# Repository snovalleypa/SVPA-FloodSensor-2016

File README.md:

# Photon-FloodSensor-2016
Particle.io Photon reading a MaxBotix I2CXL-MaxSonar via the I2C bus and pushing the data to the cloud, both as Particle.io events and to data.sparkfun.com. Forked from the 2016-2017 deployment of prototype flood sensors by the Snoqualmie Valley Preservation Alliance and modified to work with the Photon.

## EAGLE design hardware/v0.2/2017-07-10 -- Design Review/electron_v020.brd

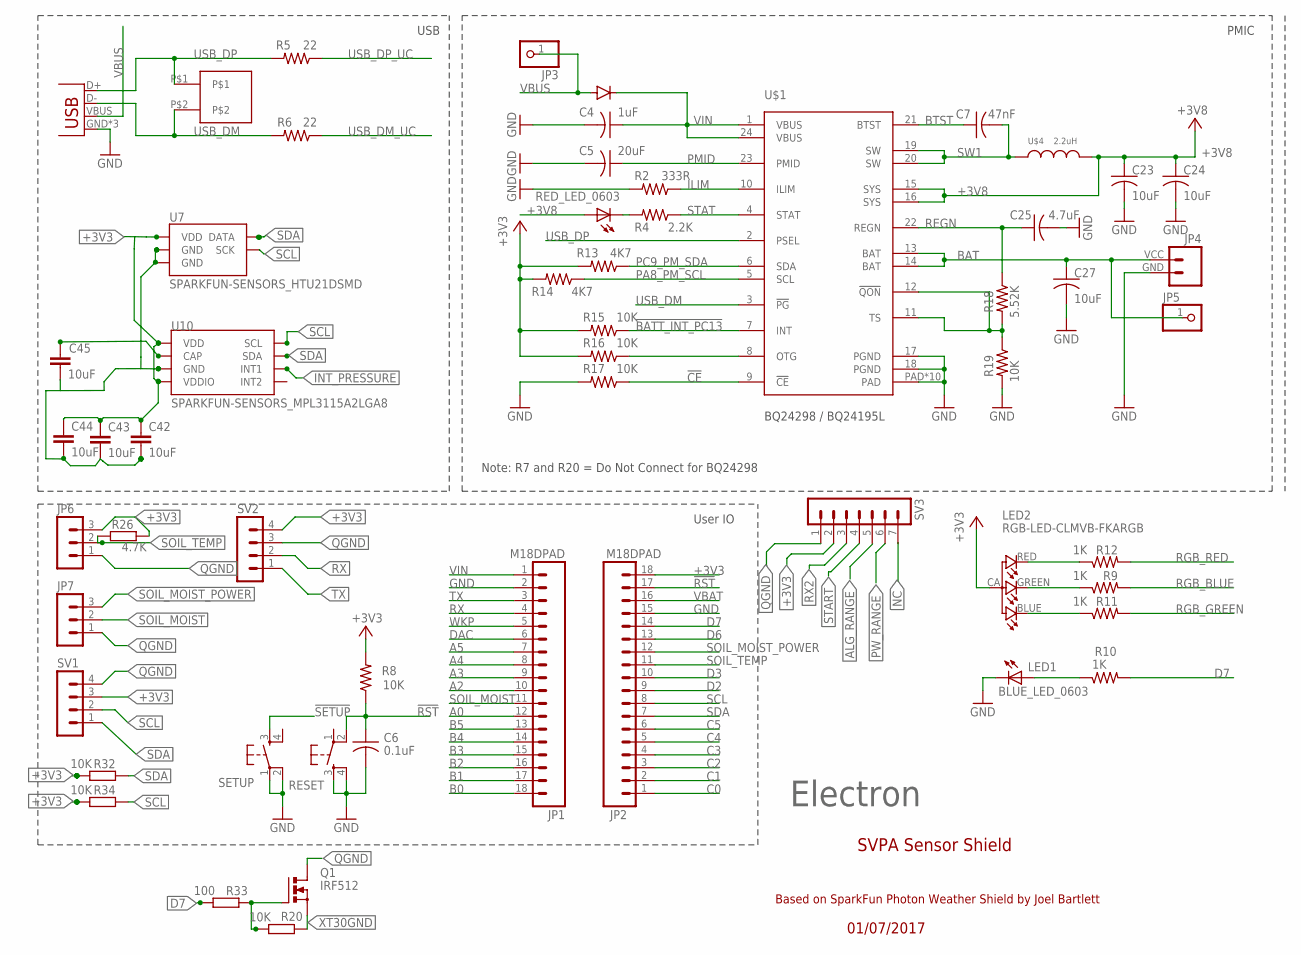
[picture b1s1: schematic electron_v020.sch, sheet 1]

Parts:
BLUE_LED_0603: LEDNOSILK; LED-0603-NS
C4: 1uF; C0603_B
C5: 20uF; C0603_B
C6: 0.1uF; C0402_B
C7: 47nF; C0402_B
C23, C24, C27: 10uF; C0603_B
C25: 4.7uF; C0603_B
C42, C43, C44, C45: 10uF; C0805
JP1, JP2: M18DPAD; 1X18-D-PADS
JP3, JP5: PINHD-1X1NOSILK; 1X01_NO_SILK
JP4: M024UCON-15767; JST-2-SMD-VERT
JP6, JP7: MA03-1
LED2: RGB-LED-CLMVB-FKARGB; PLCC4-2MM-RGB
Q1: IRF512; TO220BV
R2: 333R; R0402_B
R4: 2.2K; R0402_B
R5, R6: 22; R0402_B
R8, R15, R16, R17, R19: 10K; R0402_B
R9, R10, R11, R12: 1K; R0402_B
R13, R14: 4K7; R0402_B
R18: 5.52K; R0402_B
R20, R32, R34: 10K; R0805
R26: 4.7K; R0805
R33: 100; R0805
RED_LED_0603: LED0603; LED-0603
RESET: KMR211GLFS; TACTILE_SWITCH_SMD
SETUP: KMR211GLFS; TACTILE_SWITCH_SMD
SV1, SV2: MA04-1
SV3: MA07-1
U7: SPARKFUN-SENSORS_HTU21DSMD; SPARKFUN-SENSORS_HTU21D
U10: SPARKFUN-SENSORS_MPL3115A2LGA8; SPARKFUN-SENSORS_LGA8
U$1: BQ24298 / BQ24195L; QFN24
U$3: DIODE_NT; DIODE-DO-220AA_NT(SMP)
U$4: 2.2uH; 4020TYPE_NT
U$7: M02_0.05_HEADER
X1: USB-MICROB; USB-MICROB-SLOT-HOLE

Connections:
!BATT_INT_PC13: R15.1, U$1.7 (INT); also elsewhere on the board
!CE: R17.1, U$1.9 (!CE)
!RST: C6.1, JP2.17, R8.1, RESET.2; also elsewhere on the board
!SETUP: SETUP.3; also elsewhere on the board
+3V3: C42.1, C43.1, C44.1, JP2.18, JP6.3, LED2.CA (1), R8.2, R13.2, R14.2, R15.2, R16.2, R32.1, R34.1, SV1.3, SV2.4, U7.VDD, U10.1 (VDD), U10.4 (VDDIO); also elsewhere on the board
+3V8: C23.1, C24.1, RED_LED_0603.A, U$1.15 (SYS), U$1.16 (SYS), U$4.P$2 (2); also elsewhere on the board
A0: JP1.12; also elsewhere on the board
A2: JP1.10; also elsewhere on the board
A3: JP1.9; also elsewhere on the board
A4: JP1.8; also elsewhere on the board
A5: JP1.7; also elsewhere on the board
B0: JP1.18; also elsewhere on the board
B1: JP1.17; also elsewhere on the board
B2: JP1.16; also elsewhere on the board
B3: JP1.15; also elsewhere on the board
B4: JP1.14; also elsewhere on the board
B5: JP1.13; also elsewhere on the board
BAT: C27.1, JP4.VCC (2), JP5.1, U$1.13 (BAT), U$1.14 (BAT); also elsewhere on the board
BTST: C7.1, U$1.21 (BTST)
C0: JP2.1; also elsewhere on the board
C1: JP2.2; also elsewhere on the board
C2: JP2.3; also elsewhere on the board
C3: JP2.4; also elsewhere on the board
C4: JP2.5; also elsewhere on the board
C5: JP2.6; also elsewhere on the board
D2: JP2.9; also elsewhere on the board
D3: JP2.10; also elsewhere on the board
D6: JP2.13; also elsewhere on the board
D7: JP2.14, R10.2, R33.1; also elsewhere on the board
DAC: JP1.6; also elsewhere on the board
ILIM: R2.1, U$1.10 (ILIM)
INT_PRESSURE: U10.6 (INT1)
LED1: BLUE_LED_0603.A, R10.1
unnamed: R4.2, RED_LED_0603.C
unnamed: R16.1, U$1.8 (OTG)
unnamed: C45.1, U10.2 (CAP)
unnamed: LED2.BLUE (2), R11.1
unnamed: LED2.GREEN (3), R9.1
unnamed: Q1.G, R20.1, R33.2
unnamed: LED2.RED (4), R12.1
PA8_PM_SCL: R14.1, U$1.5 (SCL); also elsewhere on the board
PC9_PM_SDA: R13.1, U$1.6 (SDA); also elsewhere on the board
PMID: C5.1, U$1.23 (PMID)
QGND: C42.2, C43.2, C44.2, JP6.1, JP7.1, Q1.D, SV1.4, SV2.3, U7.7 (GND), U7.GND, U10.3 (GND)
REGN: C25.1, R18.1, U$1.22 (REGN)
RGB_BLUE: R11.2; also elsewhere on the board
RGB_GREEN: R9.2; also elsewhere on the board
RGB_RED: R12.2; also elsewhere on the board
RX: JP1.4, SV2.2; also elsewhere on the board
SCL: JP2.8, R34.2, SV1.2, U7.SCK, U10.8 (SCL)
SDA: JP2.7, R32.2, SV1.1, U10.7 (SDA)
SOIL_MOIST: JP1.11, JP7.2
SOIL_MOIST_POWER: JP2.12, JP7.3
SOIL_TEMP: JP2.11, JP6.2
STAT: R4.1, U$1.4 (STAT)
SW1: C7.2, U$1.19 (SW), U$1.20 (SW), U$4.P$1 (1)
TS: R18.2, R19.1, U$1.11 (TS), U$1.12 (!QON)
TX: JP1.3, SV2.1; also elsewhere on the board
USB_DM: R6.2, U$1.3 (!PG), U$7.P$2, X1.D-
USB_DM_UC: R6.1; also elsewhere on the board
USB_DP: R5.2, U$1.2 (PSEL), U$7.P$1, X1.D+
USB_DP_UC: R5.1; also elsewhere on the board
VBAT: JP2.16; also elsewhere on the board
VBUS: JP3.1, U$3.ANODE, X1.VBUS
VIN: C4.1, JP1.1, U$1.1 (VBUS), U$1.24 (VBUS), U$3.CATHODE
WKP: JP1.5; also elsewhere on the board

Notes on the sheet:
PMIC
User IO
USB
Electron
Note: R7 and R20 = Do Not Connect for BQ24298
01/07/2017
SVPA Sensor Shield
Based on SparkFun Photon Weather Shield by Joel Bartlett

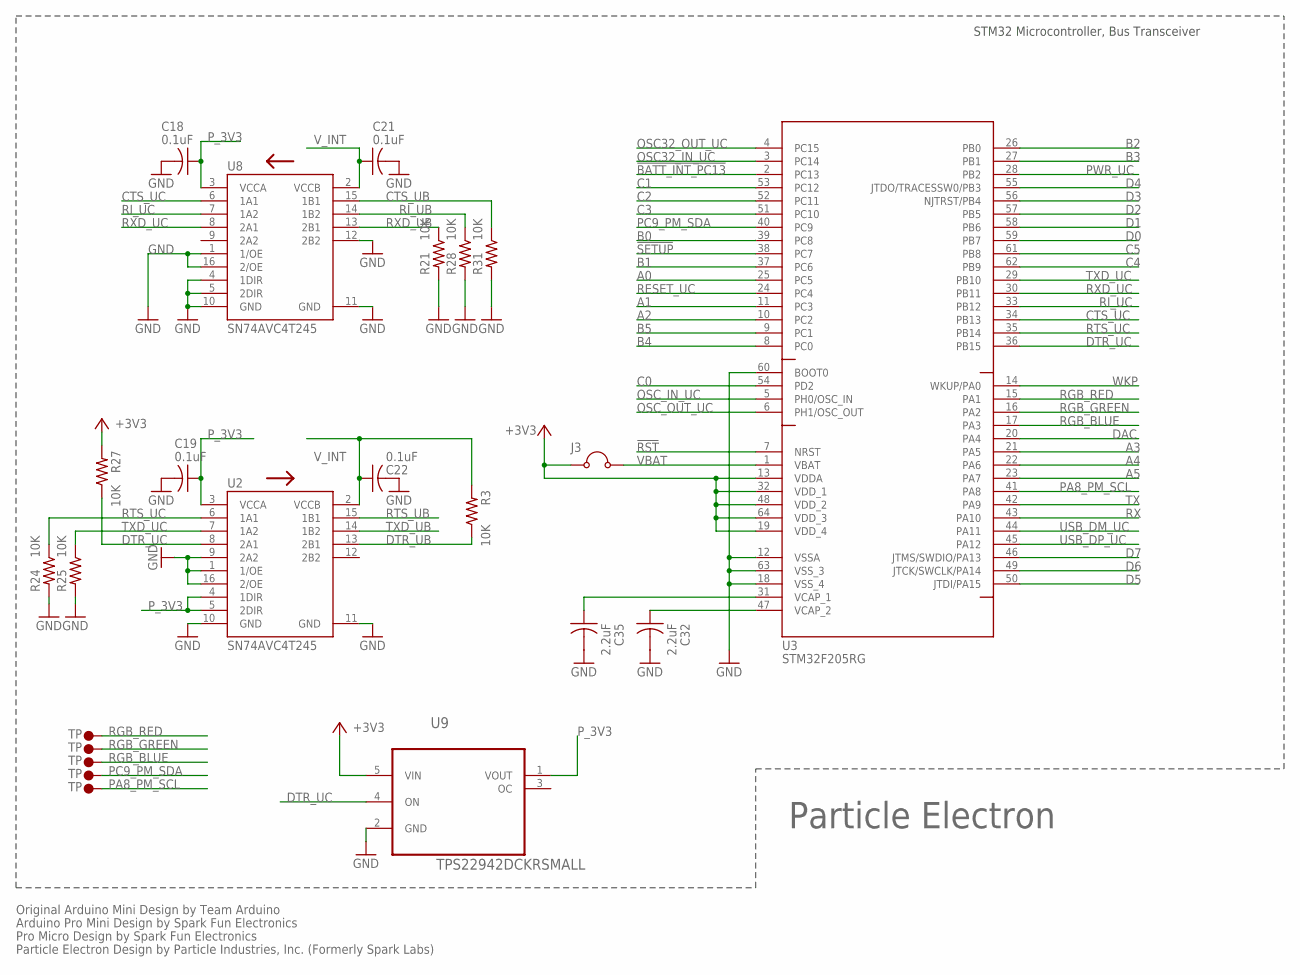
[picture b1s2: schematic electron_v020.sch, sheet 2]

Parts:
C18, C19, C21, C22: 0.1uF; C0402_B
C32, C35: 2.2uF; C0402_B
J3: JUMPER_NC_SMD; JUMPER_SMD_NC
R3, R21, R24, R25, R27, R28, R31: 10K; R0402_B
U2, U8: SN74AVC4T245; UFQFN-16
U3: STM32F205RG; LQFP64
U9: TPS22942DCKRSMALL; SC70-5
U$8, U$9, U$11, U$12, U$13: TP0; TP30_BOT

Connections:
!BATT_INT_PC13: U3.2 (PC13); also elsewhere on the board
!RST: U3.7 (NRST); also elsewhere on the board
!SETUP: U3.38 (PC7); also elsewhere on the board
+3V3: J3.1, R27.2, U3.13 (VDDA), U3.19 (VDD_4), U3.32 (VDD_1), U3.48 (VDD_2), U3.64 (VDD_3), U9.5 (VIN); also elsewhere on the board
A0: U3.25 (PC5); also elsewhere on the board
A1: U3.11 (PC3)
A2: U3.10 (PC2); also elsewhere on the board
A3: U3.21 (PA5); also elsewhere on the board
A4: U3.22 (PA6); also elsewhere on the board
A5: U3.23 (PA7); also elsewhere on the board
B0: U3.39 (PC8); also elsewhere on the board
B1: U3.37 (PC6); also elsewhere on the board
B2: U3.26 (PB0); also elsewhere on the board
B3: U3.27 (PB1); also elsewhere on the board
B4: U3.8 (PC0); also elsewhere on the board
B5: U3.9 (PC1); also elsewhere on the board
C0: U3.54 (PD2); also elsewhere on the board
C1: U3.53 (PC12); also elsewhere on the board
C2: U3.52 (PC11); also elsewhere on the board
C3: U3.51 (PC10); also elsewhere on the board
C4: U3.62 (PB9); also elsewhere on the board
C5: U3.61 (PB8); also elsewhere on the board
CTS_UB: R31.1, U8.15 (1B1); also elsewhere on the board
CTS_UC: U3.34 (PB13), U8.6 (1A1)
D0: U3.59 (PB7)
D1: U3.58 (PB6)
D2: U3.57 (PB5); also elsewhere on the board
D3: U3.56 (NJTRST/PB4); also elsewhere on the board
D4: U3.55 (JTDO/TRACESSW0/PB3)
D5: U3.50 (JTDI/PA15)
D6: U3.49 (JTCK/SWCLK/PA14); also elsewhere on the board
D7: U3.46 (JTMS/SWDIO/PA13); also elsewhere on the board
DAC: U3.20 (PA4); also elsewhere on the board
DTR_UB: R3.1, U2.13 (2B1); also elsewhere on the board
DTR_UC: R27.1, U2.8 (2A1), U3.36 (PB15), U9.4 (ON)
unnamed: C35.1, U3.31 (VCAP_1)
unnamed: C32.1, U3.47 (VCAP_2)
OSC32_IN_UC: U3.3 (PC14); also elsewhere on the board
OSC32_OUT_UC: U3.4 (PC15); also elsewhere on the board
OSC_IN_UC: U3.5 (PH0/OSC_IN); also elsewhere on the board
OSC_OUT_UC: U3.6 (PH1/OSC_OUT); also elsewhere on the board
PA8_PM_SCL: U3.41 (PA8), U$9.P$1; also elsewhere on the board
PC9_PM_SDA: U3.40 (PC9), U$8.P$1; also elsewhere on the board
PWR_UC: U3.28 (PB2); also elsewhere on the board
P_3V3: C18.1, C19.1, U2.3 (VCCA), U2.4 (1DIR), U2.5 (2DIR), U8.3 (VCCA), U9.1 (VOUT)
RESET_UC: U3.24 (PC4); also elsewhere on the board
RGB_BLUE: U3.17 (PA3), U$13.P$1; also elsewhere on the board
RGB_GREEN: U3.16 (PA2), U$12.P$1; also elsewhere on the board
RGB_RED: U3.15 (PA1), U$11.P$1; also elsewhere on the board
RI_UB: R28.1, U8.14 (1B2); also elsewhere on the board
RI_UC: U3.33 (PB12), U8.7 (1A2)
RTS_UB: U2.15 (1B1); also elsewhere on the board
RTS_UC: R24.1, U2.6 (1A1), U3.35 (PB14)
RX: U3.43 (PA10); also elsewhere on the board
RXD_UB: R21.1, U8.13 (2B1); also elsewhere on the board
RXD_UC: U3.30 (PB11), U8.8 (2A1)
TX: U3.42 (PA9); also elsewhere on the board
TXD_UB: U2.14 (1B2); also elsewhere on the board
TXD_UC: R25.1, U2.7 (1A2), U3.29 (PB10)
USB_DM_UC: U3.44 (PA11); also elsewhere on the board
USB_DP_UC: U3.45 (PA12); also elsewhere on the board
VBAT: J3.2, U3.1 (VBAT); also elsewhere on the board
V_INT: C21.1, C22.1, R3.2, U2.2 (VCCB), U8.2 (VCCB); also elsewhere on the board
WKP: U3.14 (WKUP/PA0); also elsewhere on the board

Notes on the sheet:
Particle Electron
STM32 Microcontroller, Bus Transceiver
Original Arduino Mini Design by Team Arduino
Arduino Pro Mini Design by Spark Fun Electronics
Pro Micro Design by Spark Fun Electronics
Particle Electron Design by Particle Industries, Inc. (Formerly Spark Labs)

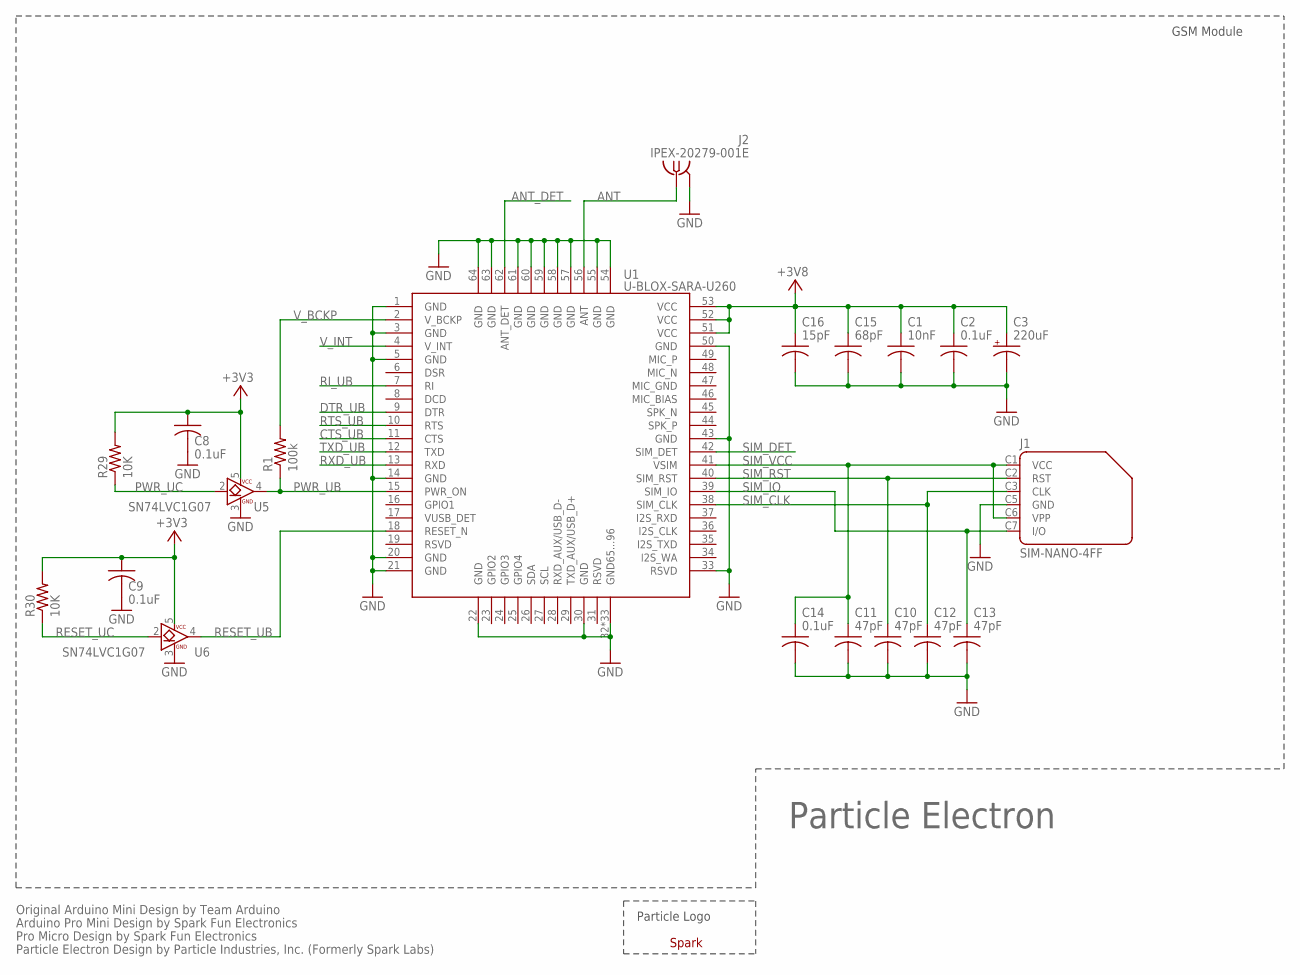
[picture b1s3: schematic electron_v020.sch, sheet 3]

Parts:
C1: 10nF; C0402_B
C2, C8, C9, C14: 0.1uF; C0402_B
C3: 220uF; C/6032-28R
C10, C11, C12, C13: 47pF; C0402_B
C15: 68pF; C0402_B
C16: 15pF; C0402_B
J1: SIM-NANO-4FF; GCT-SIM8100
J2: IPEX-20279-001E
R1: 100k; R0402_B
R29, R30: 10K; R0402_B
U1: U-BLOX-SARA-U260; U-BLOX-SARA-U2
U5, U6: SN74LVC1G07; SC-70-5
U$2: SPARK_LOGO2

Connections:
+3V3: C8.1, C9.1, R29.2, R30.2, U5.5 (VCC), U6.5 (VCC); also elsewhere on the board
+3V8: C1.1, C2.1, C3.+, C15.1, C16.1, U1.51 (VCC), U1.52 (VCC), U1.53 (VCC); also elsewhere on the board
ANT: J2.1, U1.56 (ANT)
ANT_DET: U1.62 (ANT_DET)
CTS_UB: U1.11 (CTS); also elsewhere on the board
DTR_UB: U1.9 (DTR); also elsewhere on the board
PWR_UB: R1.1, U1.15 (PWR_ON), U5.4 (B)
PWR_UC: R29.1, U5.2 (A); also elsewhere on the board
RESET_UB: U1.18 (RESET_N), U6.4 (B)
RESET_UC: R30.1, U6.2 (A); also elsewhere on the board
RI_UB: U1.7 (RI); also elsewhere on the board
RTS_UB: U1.10 (RTS); also elsewhere on the board
RXD_UB: U1.13 (RXD); also elsewhere on the board
SIM_CLK: C12.1, J1.C3 (CLK), U1.38 (SIM_CLK)
SIM_DET: U1.42 (SIM_DET)
SIM_IO: C13.1, J1.C7 (I/O), U1.39 (SIM_IO)
SIM_RST: C10.1, J1.C2 (RST), U1.40 (SIM_RST)
SIM_VCC: C11.1, C14.1, J1.C1 (VCC), J1.C6 (VPP), U1.41 (VSIM)
TXD_UB: U1.12 (TXD); also elsewhere on the board
V_BCKP: R1.2, U1.2 (V_BCKP)
V_INT: U1.4 (V_INT); also elsewhere on the board

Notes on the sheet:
Particle Electron
GSM Module
Particle Logo
Original Arduino Mini Design by Team Arduino
Arduino Pro Mini Design by Spark Fun Electronics
Pro Micro Design by Spark Fun Electronics
Particle Electron Design by Particle Industries, Inc. (Formerly Spark Labs)

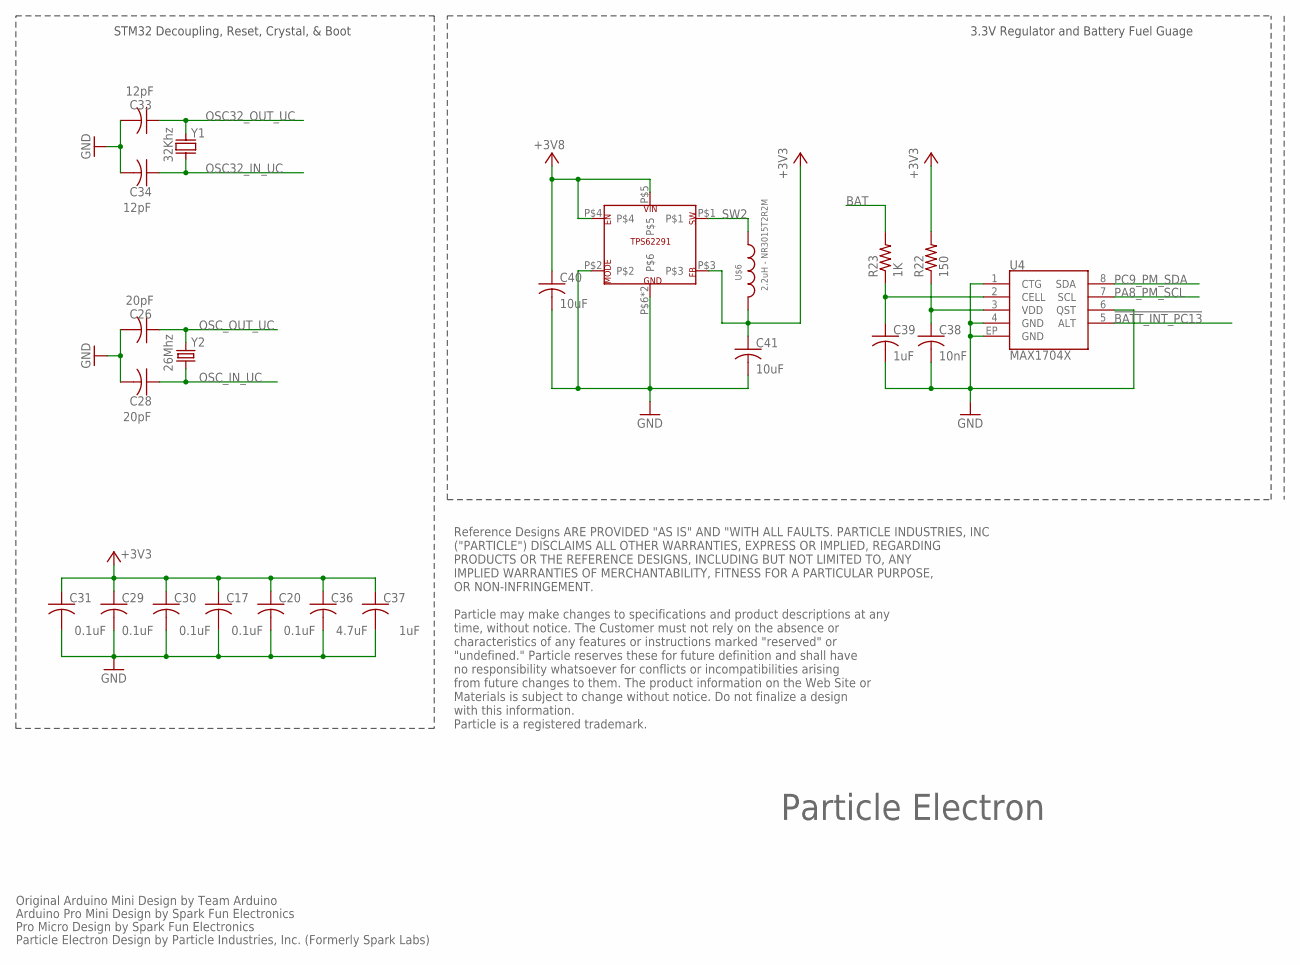
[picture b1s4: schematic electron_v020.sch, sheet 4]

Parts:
C17, C20, C29, C30, C31: 0.1uF; C0402_B
C26, C28: 20pF; C0402_B
C33, C34: 12pF; C0402_B
C36: 4.7uF; C0402_B
C37, C39: 1uF; C0402_B
C38: 10nF; C0402_B
C40, C41: 10uF; C0603_B
R22: 150; 0603-RES
R23: 1K; 0603-RES
U4: MAX1704X; TDFN-8
U$5: TPS62291DRV; S-PWSON-N6
U$6: 2.2uH - NR3015T2R2M; INDUCTOR-NR3015
Y1: 32Khz; FC135
Y2: 26Mhz; CRYSTAL-SMD-5X3

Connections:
!BATT_INT_PC13: U4.5 (ALT); also elsewhere on the board
+3V3: C17.1, C20.1, C29.1, C30.1, C31.1, C36.1, C37.1, C41.1, R22.2, U$5.P$3, U$6.2; also elsewhere on the board
+3V8: C40.1, U$5.P$4, U$5.P$5; also elsewhere on the board
BAT: R23.2; also elsewhere on the board
unnamed: C39.1, R23.1, U4.2 (CELL)
unnamed: C38.1, R22.1, U4.3 (VDD)
OSC32_IN_UC: C34.1, Y1.X1 (1); also elsewhere on the board
OSC32_OUT_UC: C33.1, Y1.X2 (2); also elsewhere on the board
OSC_IN_UC: C28.1, Y2.1; also elsewhere on the board
OSC_OUT_UC: C26.1, Y2.3 (2); also elsewhere on the board
PA8_PM_SCL: U4.7 (SCL); also elsewhere on the board
PC9_PM_SDA: U4.8 (SDA); also elsewhere on the board
SW2: U$5.P$1, U$6.1

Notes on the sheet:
Particle Electron
STM32 Decoupling, Reset, Crystal, & Boot
3.3V Regulator and Battery Fuel Guage
Original Arduino Mini Design by Team Arduino
Arduino Pro Mini Design by Spark Fun Electronics
Pro Micro Design by Spark Fun Electronics
Particle Electron Design by Particle Industries, Inc. (Formerly Spark Labs)
Reference Designs ARE PROVIDED "AS IS" AND "WITH ALL FAULTS. PARTICLE INDUSTRIES, INC ("PARTICLE") DISCLAIMS ALL OTHER WARRANTIES, EXPRESS OR IMPLIED, REGARDING PRODUCTS OR THE REFERENCE DESIGNS, INCLUDING BUT NOT LIMITED TO, ANY IMPLIED WARRANTIES OF MERCHANTABILITY, FITNESS FOR A PARTICULAR PURPO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

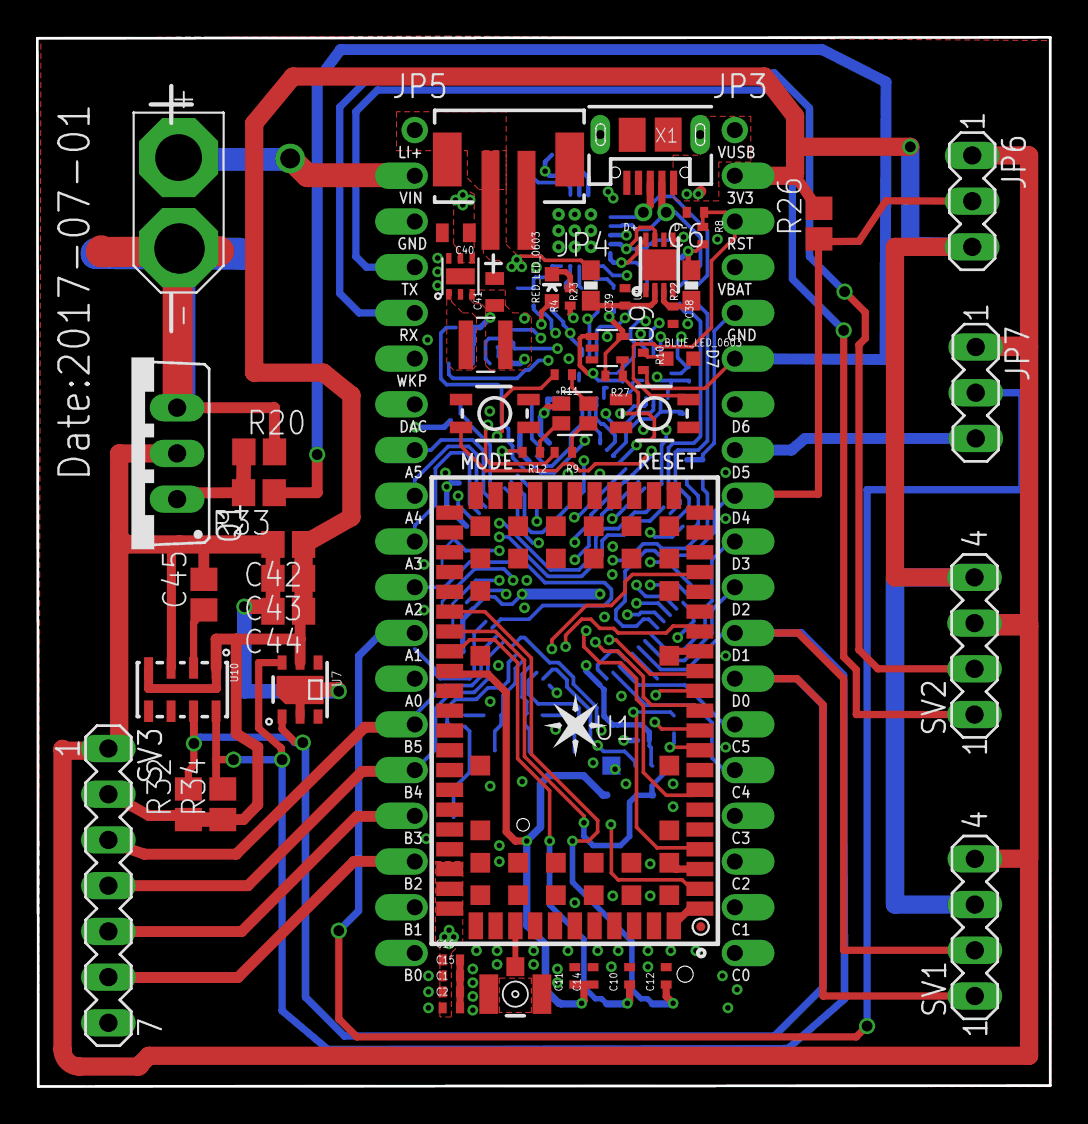
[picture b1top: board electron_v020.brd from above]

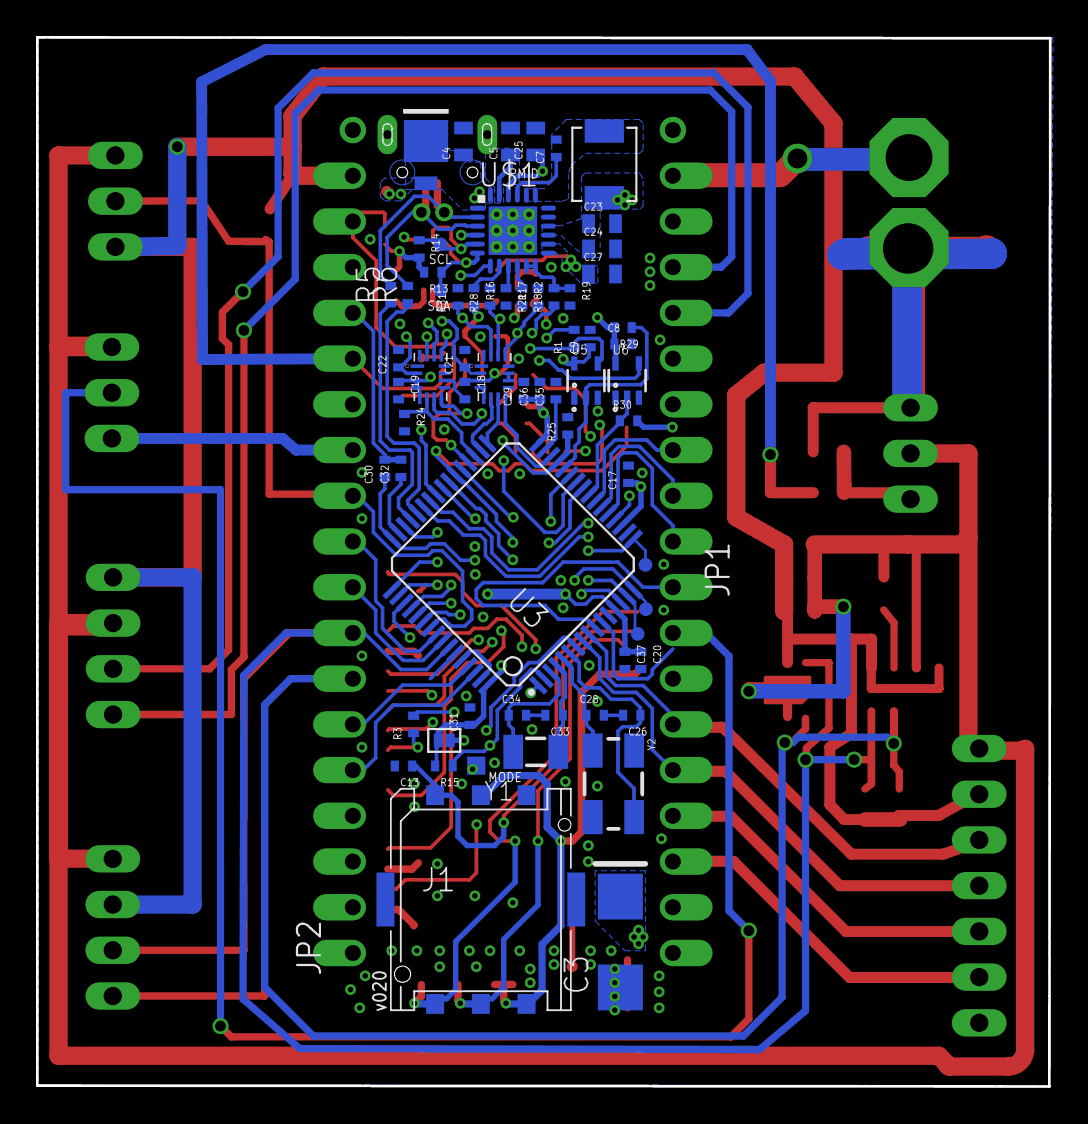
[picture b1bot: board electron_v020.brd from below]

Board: 4 copper layers, 56.3 x 58.3 mm, 123 parts (61 on the bottom side), 99 nets.

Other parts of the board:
E$1: HSPALM_XT30

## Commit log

2016-02-01 Copied from build.particle.io
2016-10-02 Initial public commit of fork from https://github.com/tsayles/Photon-I2C-RangeFinder.git with changes to support Particle.io Electron.
2016-11-02 Removed Delay(30000) that waited for OTA updates. (Duplicates change made in build v4 made during meeting.)
    Also changed sleep time from 1000 seconds (16 minutes 40 seconds) to 1200 seconds (20 minutes).
2016-11-19 started dev branch; added prototype for functionality to ensure OTA updates; started refactoring of main module to facilitate multi developer activities;
2016-11-20 implimented updates on the quarter hour using getSecUntilUpdate(); starting work on peroidic 1 minute delay for OTA updates;
2016-11-20 OTA Updater worked! Releasing as firmware build v6
2016-11-20 Debugging on sleep time
2016-11-20 Debugged and tuned getSecUntilUpdate based on testing
2016-11-20 more debugging, tuning and testing on sleep time
2016-11-28 Added status webpage files (work in progress)
2016-12-19 working on pullin updates from SVPA version
2016-12-19 still working on pullin updates from SVPA version
2016-12-19 Running version with updates from SVPA version
2016-12-19 set up as a product (#2631) on Particle.io to enable cloud push of firmware
2016-12-20 re-synced recent work from web server
2016-12-23 refactored plotSensorData as a function and plot a 2nd device
2017-01-02 commiting untested local changes before pulling from github
2017-01-12 rolling back to v7 and starting v8 over again
2017-01-12 updated devices.csv with Unit-01-Tom-WiFi for web page
2017-01-12 Starting to build consolidated JSON string. SVPA-FloodSensor-2016-v008-03
2017-01-12 More JSON Building & commenting out debug events. SVPA-FloodSensor-2016-v008-04
2017-01-12 More JSON Building, removed extra white space. SVPA-FloodSensor-2016-v008-05
2017-01-13 More JSON Building with new Report and Reading structs. SVPA-FloodSensor-2016-v008-06
2017-01-13 More JSON Building Valid ReportJSON & ReadingJSON. SVPA-FloodSensor-2016-v008-07
2017-01-13 Basic JSON Reading and Report working. SVPA-FloodSensor-2016-v008-08
2017-01-15 resyncing with live MPZap.com website
2017-01-15 updates to include filtered links to Readings stream at data.SparkFun.com
2017-01-23 Started working on v002
2017-01-23 updated README.md with Photon info
2017-01-29 Implimented circular array for lastReadings
2017-02-05 Implimented HTTP POST of full report JSON. v002 release canadate
2017-02-05 added units 11 and 12 to devices list
2017-02-05 Starting v009
2017-02-08 Implements pushing JSON Report (including last 10 readings) to an endpoint via HTTP POST request. Functionality ported from Photon version. Also moves publishData from setup() to loop().
2017-02-19 improved POST reliability. Added call to saveNewReading. Cleaned up old / irrelavant comments.
2017-02-19 Starting v011
2017-03-15 Update with new Post URL and no quotes on Time stamps. UNTESTEDgit statusgit status
2017-05-04 pushing latest for code review
2017-06-25 adding range repetitions
2017-06-26 added privateConfig.h
    prevent private data from being posted in the git hub
2017-06-26 Remove private config data
2017-06-26 abstracted range checking & point debug to serial
2017-06-26 updates to allow pull
2017-06-26 Implements SEMI AUTOMATIC sleep mode postponing radio on until after data collected
2017-06-26 Implements SEMI AUTOMATIC sleep mode postponing radio on until after data collected w/ updated comment
2017-07-05 Starting v13
2017-07-05 updated firmwareVersion to 13; also added LED flashes after data collected and before radio start
2017-08-03 adding v020 hardware files and HW reference files
2017-09-17 HTML & js Updates to pull live device list from Particle.io. Working on live event stream.
2017-09-17 cleaning up working folders (ignoring z_Archives folders) and adding hardware related files.

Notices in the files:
parts and their libraries:
SparkFun-FreqCtrl: Licensing: CC v3.0 Share-Alike You are welcome to use this library for commercial purposes.
SparkFun-Connectors: Licensing: Creative Commons ShareAlike 4.0 International - https://creativecommons.org/licenses/by-sa/4.0
